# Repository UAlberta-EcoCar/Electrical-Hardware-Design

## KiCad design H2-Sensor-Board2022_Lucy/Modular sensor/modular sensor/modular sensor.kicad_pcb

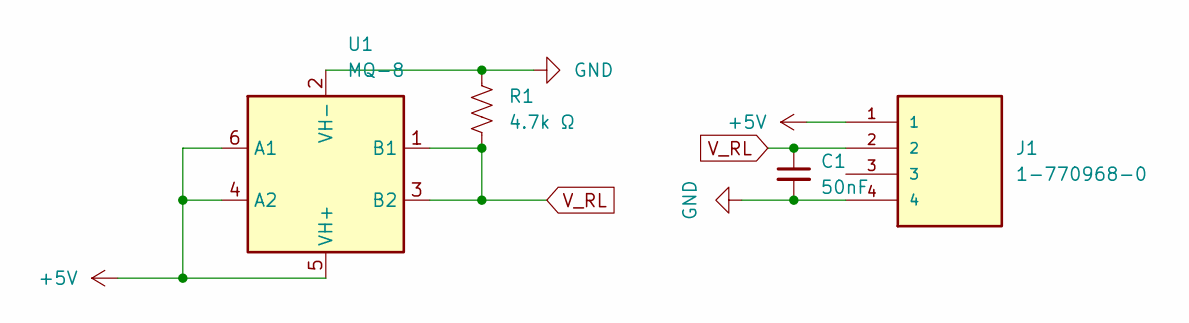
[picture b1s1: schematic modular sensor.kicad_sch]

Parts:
C1: 50nF; C_0402_1005Metric
J1: 1-770968-0; TE_1-770968-0
R1: 4.7k Ω; R_0402_1005Metric_Pad0.72x0.64mm_HandSolder
U1: MQ-8

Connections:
+5V: J1.1, U1.4 (A2), U1.5 (VH+), U1.6 (A1)
GND: C1.2, J1.4, R1.1, U1.2 (VH-)
V_RL: C1.1, J1.2, R1.2, U1.1 (B1), U1.3 (B2)

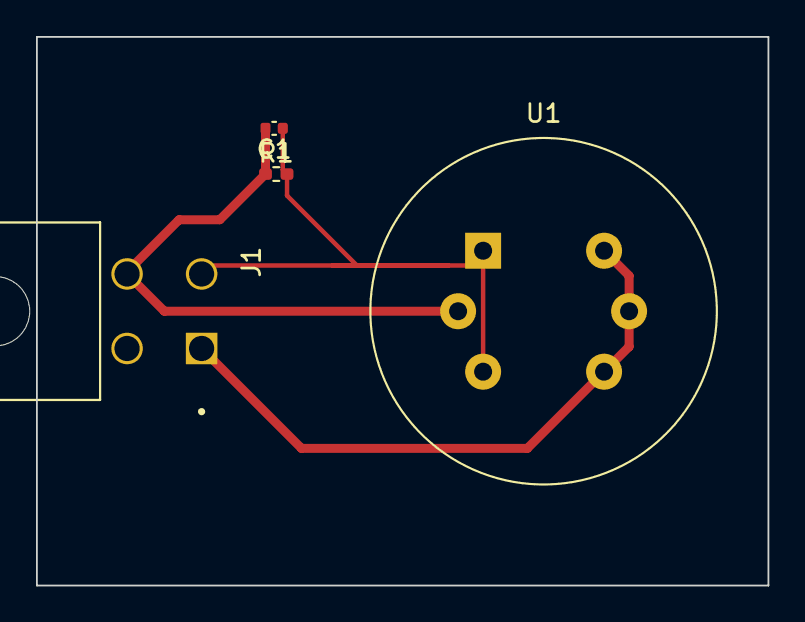
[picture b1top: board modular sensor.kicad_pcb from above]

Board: 2 copper layers, 40.6 x 30.5 mm, 4 parts (0 on the bottom side), 3 nets.

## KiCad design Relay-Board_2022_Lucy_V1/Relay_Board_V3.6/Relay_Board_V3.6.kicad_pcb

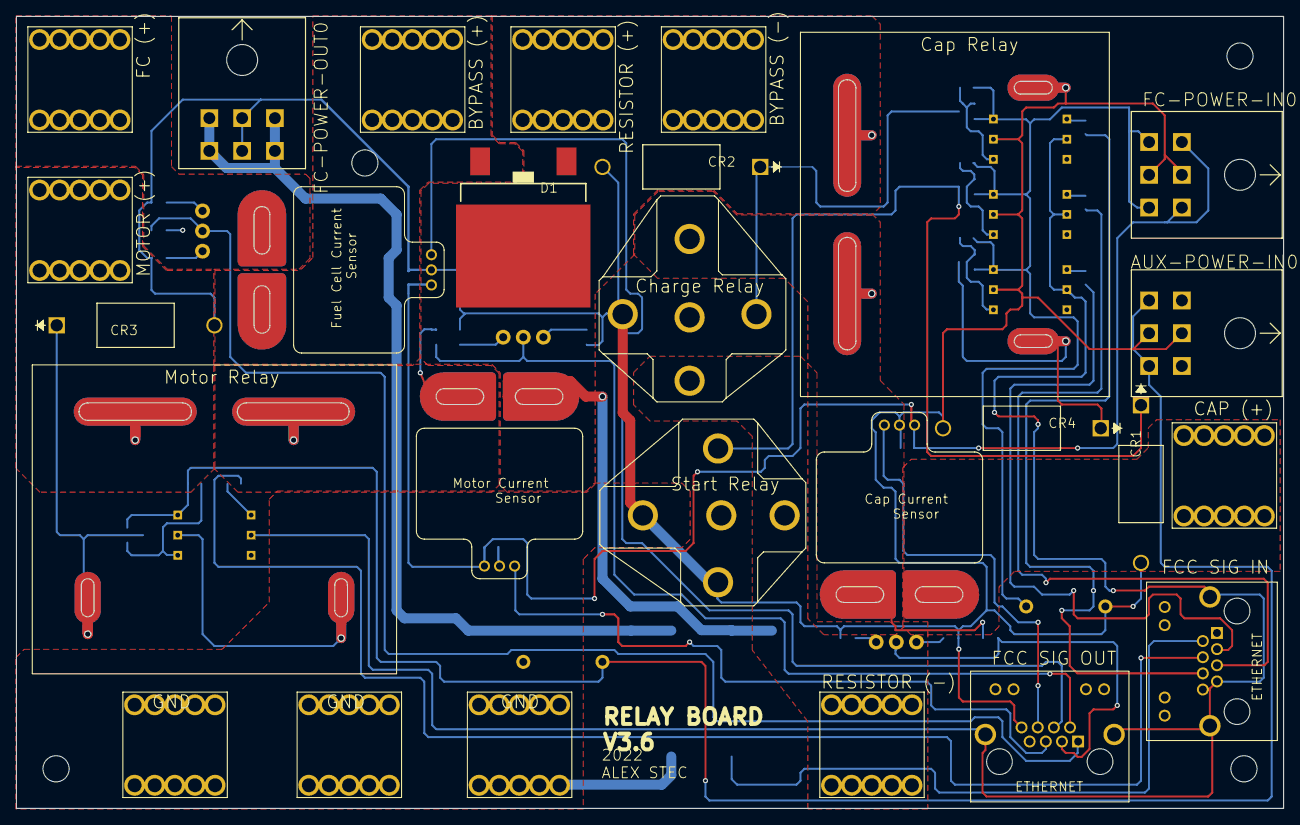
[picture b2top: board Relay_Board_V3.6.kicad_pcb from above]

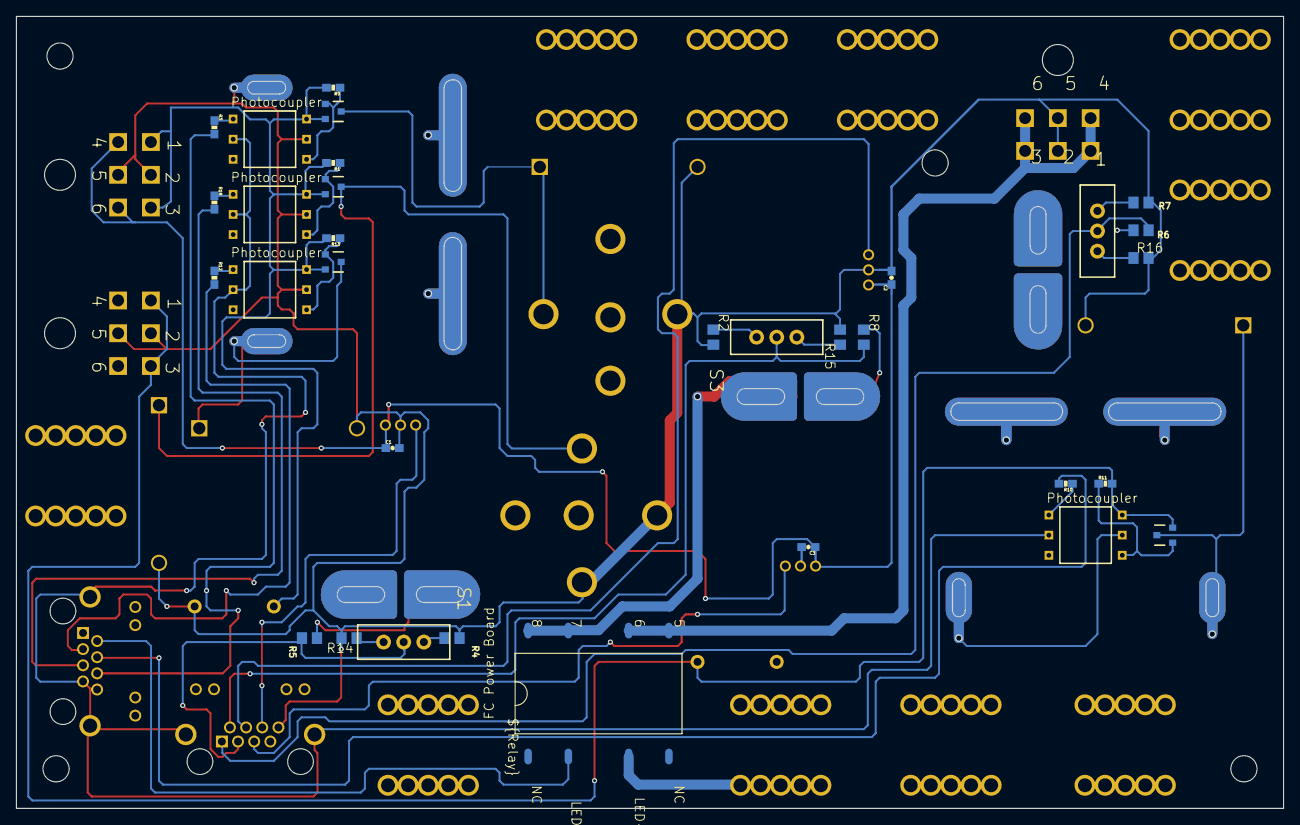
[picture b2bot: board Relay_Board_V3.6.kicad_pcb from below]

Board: 2 copper layers, 160.0 x 100.0 mm, 65 parts (32 on the bottom side), 44 nets.

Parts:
AUX-POWER-IN0: TE_6-PIN
C1, C2, C3: 0.1u; 0603-CAP
CAP.GND0, CAP.POS0, CAP.POS1, CAP.POS2: 732-3204-ND_CONNECTOR; 732-3204-ND
CR1, CR2, CR3, CR4: MUR420RLG; DO-201AD
D1: APT60S20SG; TO268
FC-POWER-IN0: TE_6-PIN
FC-POWER-OUT0: TE_6-PIN
FC.GND0, FC.POS0: 732-3204-ND_CONNECTOR; 732-3204-ND
FCC_SIG_IN0: ETHERNET; A122645-ND
FCC_SIG_OUT0: ETHERNET; A122645-ND
FC_POWER_BOARD_RELAY0: RELAY-CPC1907B
MOTOR.GROUND0, MOTOR.POSITIVE0: 732-3204-ND_CONNECTOR; 732-3204-ND
R1, R9, R11, R13: 10k; 0603-RES
R2, R4, R7: 775 (0.1%); R0805
R3, R10, R12, R18: 470; 0603-RES
R5, R6, R8: 10.5k (0.1%); R0805
R14, R15, R16: 1.5k (0.1%); R0805
RES.NEG0, RES.POS0: 732-3204-ND_CONNECTOR; 732-3204-ND
S1, S2, S3: SWITCH-SPDT
START.RELAY1, START.RELAY2: VCF4-1000
U$1, U$3, U$5, U$11: DMP3056L-7DMP3056L-7; DMP3056L-7
U$2, U$4, U$6, U$12: H11L1H11L1; H11L1
U$7, U$8, U$9: ACS770LCB_CURRENTSENSOR
U$13, U$14: 255-5246-ND
U$15, U$16: P6KE15A-E3/54GICT-ND_TVS_DIODE; P6KE15A-E3_54GICT-ND_TVS_DIODE
U$18, U$20, U$21, U$23: STAND-OFF

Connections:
5V: C1.1, C2.1, C3.1, FC-POWER-IN0.4, FC-POWER-IN0.6, U$7.PIN1, U$8.PIN1, U$9.PIN1
AUX.12: AUX-POWER-IN0.1, AUX-POWER-IN0.3, R11.2, U$3.S, U$4.VCC, U$16.P$2
CAP_CURR: FCC_SIG_OUT0.P$6, U$8.PIN3
CAP_FUSE: CAP.POS0.P$1, CAP.POS0.P$2, CAP.POS0.P$3, CAP.POS0.P$4, CAP.POS0.P$5, CAP.POS0.P$6, CAP.POS0.P$7, CAP.POS0.P$8, CAP.POS0.P$9, CAP.POS0.P$10, U$8.PIN5
CAP_R: FCC_SIG_IN0.P$3, R12.2
CAP_SENSOR: R5.1, START.RELAY2.30, U$8.PIN4, U$13.NO(+), U$13.NO(++)
CAP_VOLT: FCC_SIG_OUT0.P$3, R5.2, S1.2
CHARGE_R: FCC_SIG_IN0.P$6, R3.2
CHARGING_RES_NEG: RES.NEG0.P$1, RES.NEG0.P$2, RES.NEG0.P$3, RES.NEG0.P$4, RES.NEG0.P$5, RES.NEG0.P$6, RES.NEG0.P$7, RES.NEG0.P$8, RES.NEG0.P$9, RES.NEG0.P$10, START.RELAY1.87, START.RELAY2.87
FC.12: FC-POWER-IN0.1, FC-POWER-IN0.3, R1.2, R9.2, R13.2, U$1.S, U$2.VCC, U$5.S, U$6.VCC, U$11.S, U$12.VCC, U$15.P$2
FC_CURR: FCC_SIG_OUT0.P$4, U$7.PIN3
FC_POS: CAP.POS2.P$1, CAP.POS2.P$2, CAP.POS2.P$3, CAP.POS2.P$4, CAP.POS2.P$5, CAP.POS2.P$6, CAP.POS2.P$7, CAP.POS2.P$8, CAP.POS2.P$9, CAP.POS2.P$10, D1.(-), D1.C@1, D1.C@2, FC_POWER_BOARD_RELAY0.7, FC_POWER_BOARD_RELAY0.8, RES.POS0.P$1, RES.POS0.P$2, RES.POS0.P$3, RES.POS0.P$4, RES.POS0.P$5, RES.POS0.P$6, RES.POS0.P$7, RES.POS0.P$8, RES.POS0.P$9, RES.POS0.P$10, U$9.PIN4, U$13.NO(-), U$13.NO(--)
FC_POWER: CAP.POS1.P$1, CAP.POS1.P$2, CAP.POS1.P$3, CAP.POS1.P$4, CAP.POS1.P$5, CAP.POS1.P$6, CAP.POS1.P$7, CAP.POS1.P$8, CAP.POS1.P$9, CAP.POS1.P$10, D1.(+), U$7.PIN5
FC_POWER_OUT: FC-POWER-OUT0.1, FC-POWER-OUT0.3, FC-POWER-OUT0.4, FC-POWER-OUT0.6, FC_POWER_BOARD_RELAY0.5, FC_POWER_BOARD_RELAY0.6
FC_R: FCC_SIG_IN0.P$2, FC_POWER_BOARD_RELAY0.LED+
FC_SENSOR: FC.POS0.P$1, FC.POS0.P$2, FC.POS0.P$3, FC.POS0.P$4, FC.POS0.P$5, FC.POS0.P$6, FC.POS0.P$7, FC.POS0.P$8, FC.POS0.P$9, FC.POS0.P$10, R6.1, U$7.PIN4
FC_VOLT: FCC_SIG_OUT0.P$1, R6.2, S2.2
GND: AUX-POWER-IN0.2, AUX-POWER-IN0.5, C1.2, C2.2, C3.2, CAP.GND0.P$1, CAP.GND0.P$2, CAP.GND0.P$3, CAP.GND0.P$4, CAP.GND0.P$5, CAP.GND0.P$6, CAP.GND0.P$7, CAP.GND0.P$8, CAP.GND0.P$9, CAP.GND0.P$10, CR1.2, CR2.2, CR3.2, CR4.2, FC-POWER-IN0.2, FC-POWER-IN0.5, FC-POWER-OUT0.2, FC-POWER-OUT0.5, FC.GND0.P$1, FC.GND0.P$2, FC.GND0.P$3, FC.GND0.P$4, FC.GND0.P$5, FC.GND0.P$6, FC.GND0.P$7, FC.GND0.P$8, FC.GND0.P$9, FC.GND0.P$10, FCC_SIG_OUT0.P$8, FC_POWER_BOARD_RELAY0.LED-, MOTOR.GROUND0.P$1, MOTOR.GROUND0.P$2, MOTOR.GROUND0.P$3, MOTOR.GROUND0.P$4, MOTOR.GROUND0.P$5, MOTOR.GROUND0.P$6, MOTOR.GROUND0.P$7, MOTOR.GROUND0.P$8, MOTOR.GROUND0.P$9, MOTOR.GROUND0.P$10, R2.2, R4.2, R7.2, R14.2, R15.2, R16.2, START.RELAY1.30, START.RELAY1.85, START.RELAY2.85, U$2.GND, U$4.GND, U$6.GND, U$7.PIN2, U$8.PIN2, U$9.PIN2, U$12.GND, U$13.(-), U$13.(--), U$14.(-), U$14.(--), U$15.P$1, U$16.P$1
ISO_GND: FCC_SIG_IN0.P$7, FCC_SIG_IN0.P$8, FCC_SIG_IN0.P$13, FCC_SIG_IN0.P$14, FCC_SIG_OUT0.P$13, FCC_SIG_OUT0.P$14, U$2.CATHODE, U$4.CATHODE, U$6.CATHODE, U$12.CATHODE
MOTOR_CURR: FCC_SIG_OUT0.P$5, U$9.PIN3
MOTOR_C_SENSOR: R8.1, U$9.PIN5, U$14.NO(-), U$14.NO(--)
MOTOR_POS: MOTOR.POSITIVE0.P$1, MOTOR.POSITIVE0.P$2, MOTOR.POSITIVE0.P$3, MOTOR.POSITIVE0.P$4, MOTOR.POSITIVE0.P$5, MOTOR.POSITIVE0.P$6, MOTOR.POSITIVE0.P$7, MOTOR.POSITIVE0.P$8, MOTOR.POSITIVE0.P$9, MOTOR.POSITIVE0.P$10, U$14.NO(+), U$14.NO(++)
MOTOR_R: FCC_SIG_IN0.P$4, R10.2
MOTOR_VOLT: FCC_SIG_OUT0.P$2, R8.2, S3.2
unnamed: R9.1, U$1.G, U$2.VO
unnamed: R3.1, U$2.ANODE
unnamed: CR2.1, START.RELAY2.86, U$1.D
unnamed: R11.1, U$3.G, U$4.VO
unnamed: R10.1, U$4.ANODE
unnamed: CR3.1, U$3.D, U$14.(+), U$14.(++)
unnamed: R13.1, U$5.G, U$6.VO
unnamed: R12.1, U$6.ANODE
unnamed: R4.1, S1.1
unnamed: R14.1, S1.3
unnamed: R2.1, S3.1
unnamed: R15.1, S3.3
unnamed: CR4.1, U$5.D, U$13.(+), U$13.(++)
unnamed: R7.1, S2.1
unnamed: R16.1, S2.3
unnamed: R1.1, U$11.G, U$12.VO
unnamed: R18.1, U$12.ANODE
unnamed: CR1.1, START.RELAY1.86, U$11.D
NC: FCC_SIG_IN0.P$1, FCC_SIG_OUT0.P$7
START_R: FCC_SIG_IN0.P$5, R18.2

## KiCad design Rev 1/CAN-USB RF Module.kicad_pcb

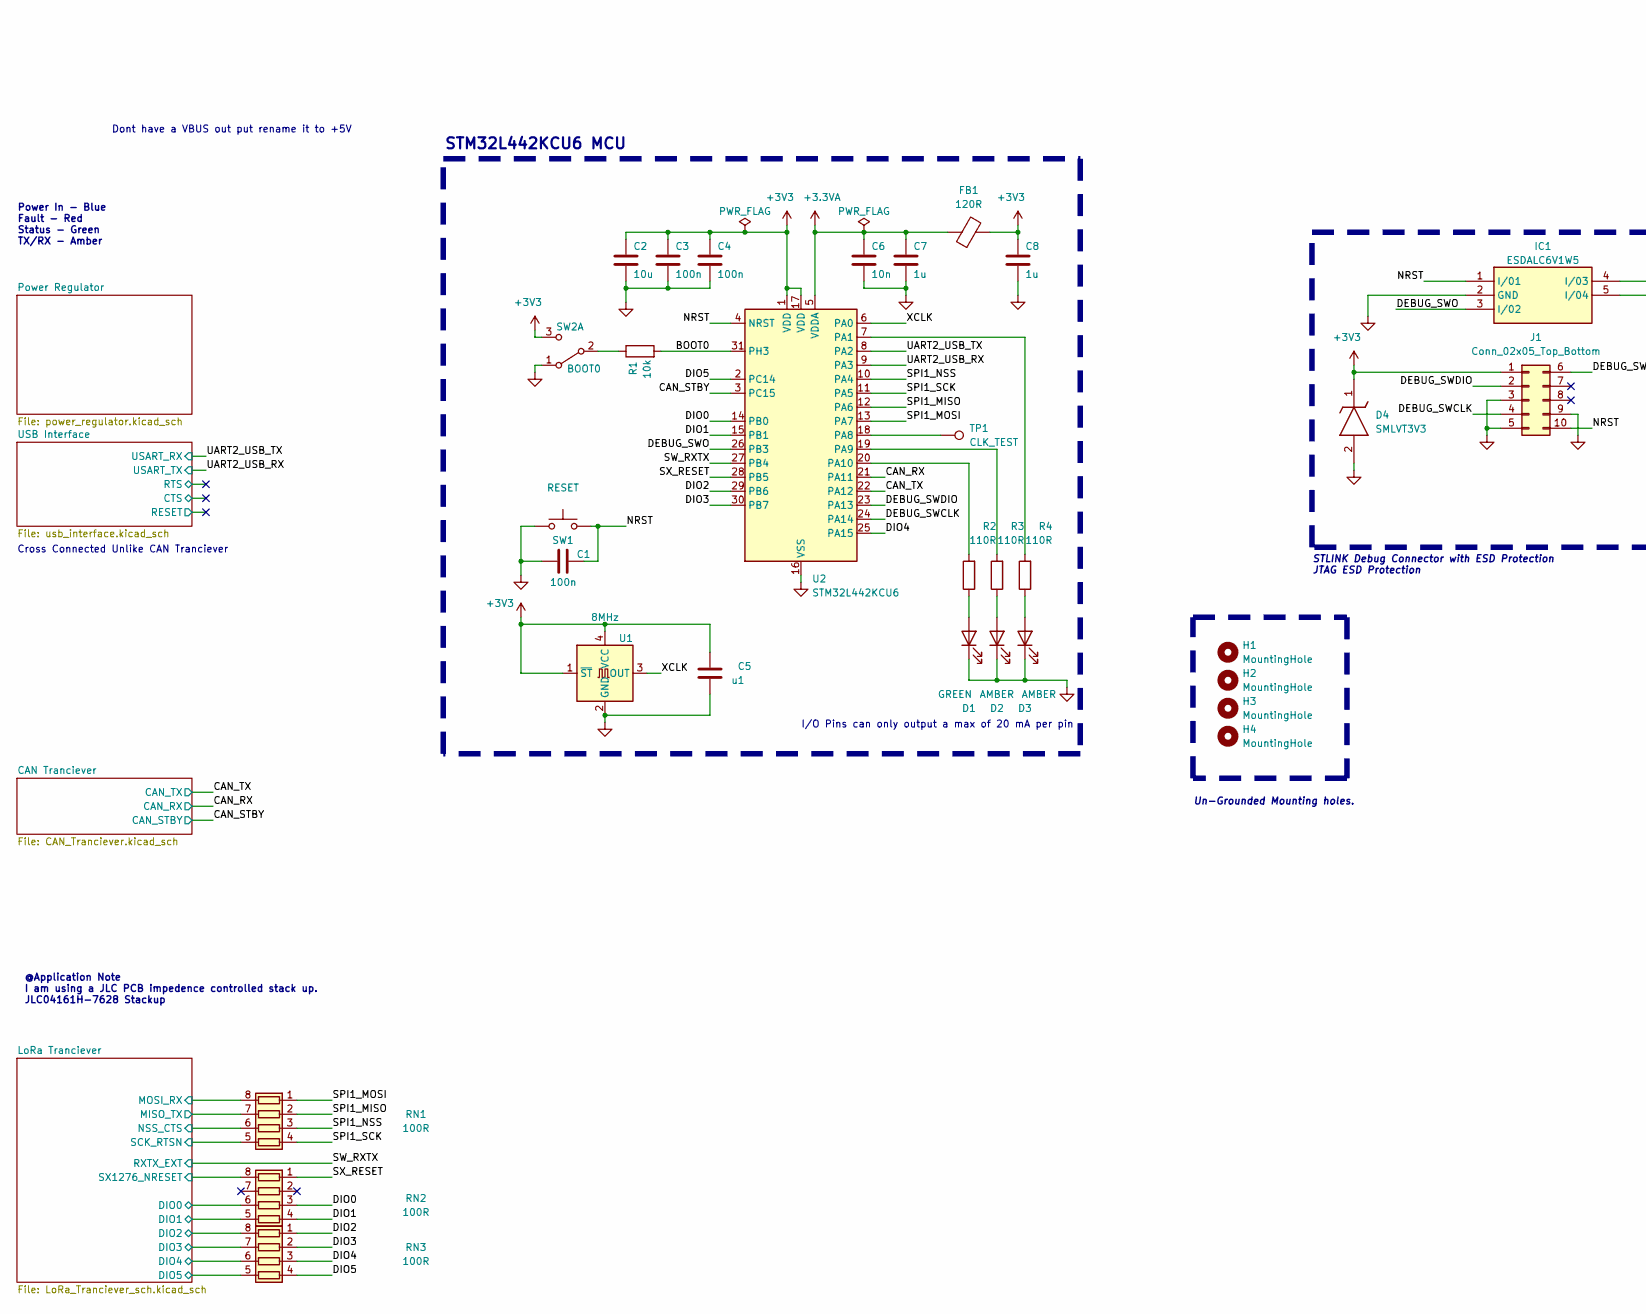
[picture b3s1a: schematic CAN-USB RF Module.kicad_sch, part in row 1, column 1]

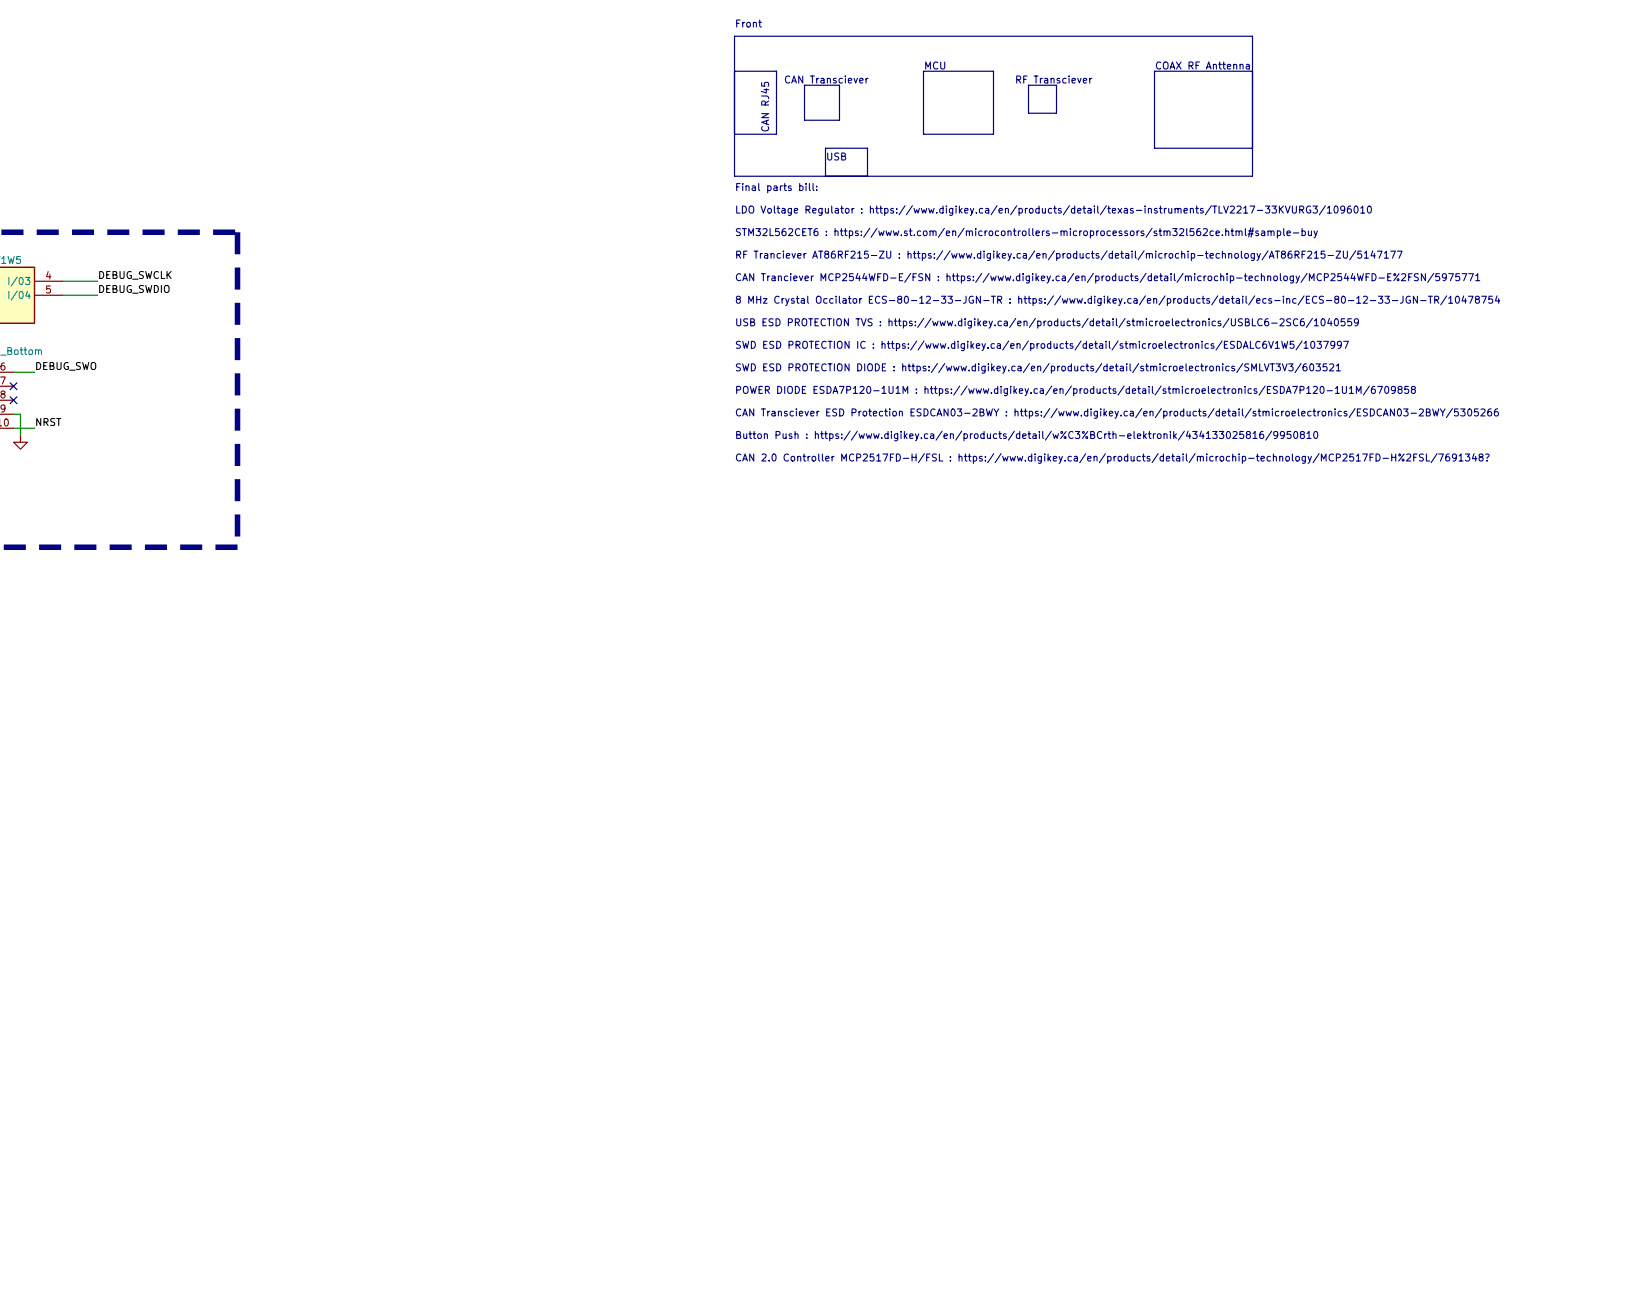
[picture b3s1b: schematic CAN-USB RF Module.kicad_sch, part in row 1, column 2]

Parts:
C1, C3, C4: 100n; C_0402_1005Metric; LCSC # C1525
C2: 10u; C_0805_2012Metric; MPN CL21B106KOQNNNE; LCSC # C95841
C5: u1; C_0402_1005Metric; LCSC # C541464
C6: 10n; C_0402_1005Metric; LCSC # C1525
C7, C8: 1u; C_0402_1005Metric; LCSC # C528974
D1: GREEN; LED_0603_1608Metric; LCSC # C72043
D2, D3: AMBER; LED_0603_1608Metric; LCSC # C2842814
D4: SMLVT3V3; DIOM5436X265N; LCSC # C283619
FB1: 120R; R_0603_1608Metric; LCSC # C62708
H1, H2, H3, H4: MountingHole; MountingHole_2.2mm_M2
IC1: ESDALC6V1W5; SOT65P210X110-5N; LCSC # C2827626
J1: Conn_02x05_Top_Bottom; PinHeader_2x05_P2.54mm_Vertical; LCSC # C5116482
R1: 10k; R_0603_1608Metric; LCSC # C25531
R2, R3, R4: 110R; R_0603_1608Metric; LCSC # C138064
RN1, RN2, RN3: 100R; R_Array_Concave_4x0402; LCSC # C48442
SW1: RESET; SW_SPST_PTS810; LCSC # C221896
SW2: BOOT0; SW_SPDT_PCM12; LCSC # C221841
TP1: CLK_TEST; TestPoint_Pad_D1.0mm
U1: 8MHz; Crystal_SMD_3225-4Pin_3.2x2.5mm; LCSC # C558766
U2: STM32L442KCU6; QFN-32-1EP_5x5mm_P0.5mm_EP3.45x3.45mm; LCSC # C2969865

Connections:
+3.3VA: C6.1, C7.1, FB1.1, U2.5 (VDDA)
+3V3: C2.1, C3.1, C4.1, C5.2, C8.1, D4.1 (K), FB1.2, J1.1, SW2.3 (C), U1.1 (~ST), U1.4 (VCC), U2.1 (VDD), U2.17 (VDD); also elsewhere on the board
/BOOT0: R1.2, U2.31 (PH3)
/CAN_RX: U2.21 (PA11); also elsewhere on the board
/CAN_STBY: U2.3 (PC15); also elsewhere on the board
/CAN_TX: U2.22 (PA12); also elsewhere on the board
/DEBUG_SWCLK: IC1.4 (I/03), J1.4, U2.24 (PA14)
/DEBUG_SWDIO: IC1.5 (I/04), J1.2, U2.23 (PA13)
/DEBUG_SWO: IC1.3 (I/02), J1.6, U2.26 (PB3)
/DIO0: RN2.3 (R3.1), U2.14 (PB0)
/DIO1: RN2.4 (R4.1), U2.15 (PB1)
/DIO2: RN3.1 (R1.1), U2.29 (PB6)
/DIO3: RN3.2 (R2.1), U2.30 (PB7)
/DIO4: RN3.3 (R3.1), U2.25 (PA15)
/DIO5: RN3.4 (R4.1), U2.2 (PC14)
/LoRa Tranciever/DIO0: RN2.6 (R3.2); also elsewhere on the board
/LoRa Tranciever/DIO1: RN2.5 (R4.2); also elsewhere on the board
/LoRa Tranciever/DIO2: RN3.8 (R1.2); also elsewhere on the board
/LoRa Tranciever/DIO3: RN3.7 (R2.2); also elsewhere on the board
/LoRa Tranciever/DIO4: RN3.6 (R3.2); also elsewhere on the board
/LoRa Tranciever/DIO5: RN3.5 (R4.2); also elsewhere on the board
/LoRa Tranciever/MISO_TX: RN1.7 (R2.2); also elsewhere on the board
/LoRa Tranciever/MOSI_RX: RN1.8 (R1.2); also elsewhere on the board
/LoRa Tranciever/NSS_CTS: RN1.6 (R3.2); also elsewhere on the board
/LoRa Tranciever/SCK_RTSN: RN1.5 (R4.2); also elsewhere on the board
/LoRa Tranciever/SX1276_NRESET: RN2.8 (R1.2); also elsewhere on the board
/NRST: C1.2, IC1.1 (I/01), J1.10, SW1.2, U2.4 (NRST)
/SPI1_MISO: RN1.2 (R2.1), U2.12 (PA6)
/SPI1_MOSI: RN1.1 (R1.1), U2.13 (PA7)
/SPI1_NSS: RN1.3 (R3.1), U2.10 (PA4)
/SPI1_SCK: RN1.4 (R4.1), U2.11 (PA5)
/SW_RXTX: U2.27 (PB4); also elsewhere on the board
/SX_RESET: RN2.1 (R1.1), U2.28 (PB5)
/UART2_USB_RX: U2.9 (PA3); also elsewhere on the board
/UART2_USB_TX: U2.8 (PA2); also elsewhere on the board
/XCLK: U1.3 (OUT), U2.6 (PA0)
GND: C1.1, C2.2, C3.2, C4.2, C5.1, C6.2, C7.2, C8.2, D1.1 (K), D2.1 (K), D3.1 (K), D4.2 (A), IC1.2 (GND), J1.3, J1.5, J1.9, SW1.1, SW2.1 (A), U1.2 (GND), U2.16 (VSS), U2.32 (VSS), U2.33 (VSS); also elsewhere on the board
unnamed: D1.2 (A), R2.1
unnamed: D2.2 (A), R3.1
unnamed: D3.2 (A), R4.1
unnamed: R1.1, SW2.2 (B)
unnamed: R4.2, U2.7 (PA1)
unnamed: TP1.1, U2.18 (PA8)
unnamed: R3.2, U2.19 (PA9)
unnamed: R2.2, U2.20 (PA10)

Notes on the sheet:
MCU
Front
Un-Grounded Mounting holes.
COAX RF Anttenna
Final parts bill: LDO Voltage Regulator : https://www.digikey.ca/en/products/detail/texas-instruments/TLV2217-33KVURG3/1096010 STM32L562CET6 : https://www.st.com/en/microcontrollers-microprocessors/stm32l562ce.html#sample-buy RF Tranciever AT86RF215-ZU : https://www.digikey.ca/en/products/detail/mi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
STM32L442KCU6 MCU
CAN Transciever
STLINK Debug Connector with ESD Protection JTAG ESD Protection
@Application Note I am using a JLC PCB impedence controlled stack up. JLC04161H-7628 Stackup
Power In - Blue Fault - Red Status - Green TX/RX - Amber
USB
Cross Connected Unlike CAN Tranciever
I/O Pins can only output a max of 20 mA per pin
CAN RJ45
RF Transciever
Dont have a VBUS out put rename it to +5V

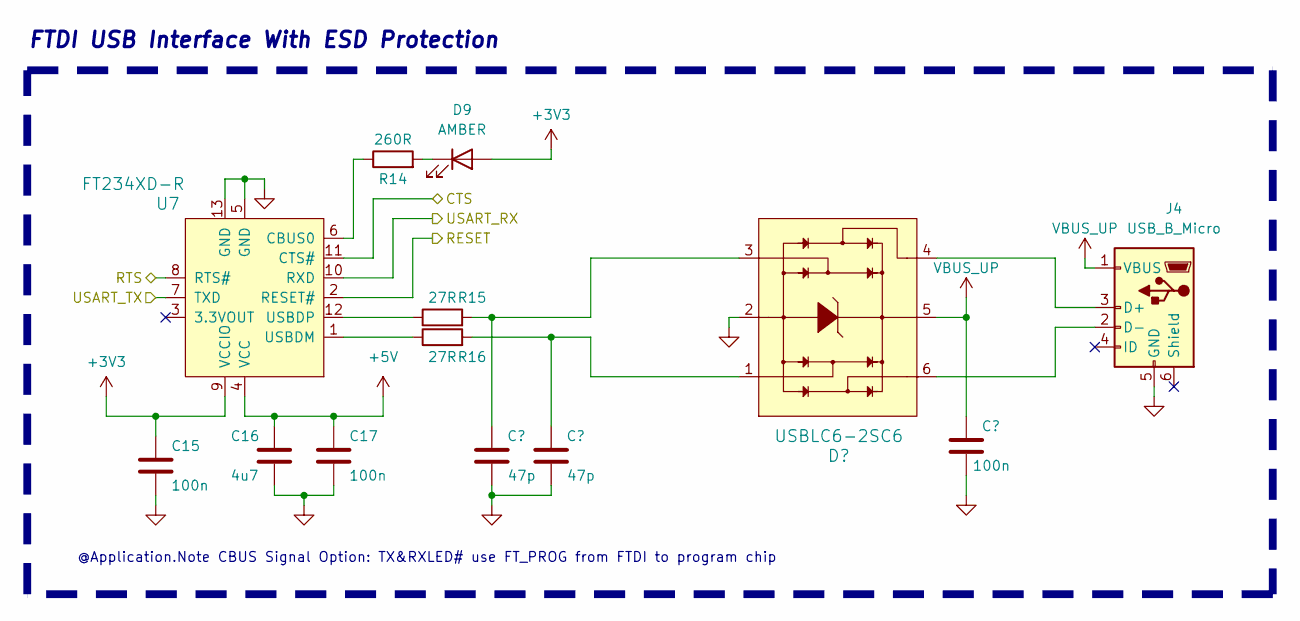
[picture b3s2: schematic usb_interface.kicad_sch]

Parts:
C15, C17, C20: 100n; C_0402_1005Metric; LCSC # C1525
C16: 4u7; C_0603_1608Metric; LCSC # C307423
C18, C19: 47p; C_0402_1005Metric; LCSC # C1567
D9: AMBER; LED_0603_1608Metric; LCSC # C2842814
D10: USBLC6-2SC6; SOT23-6L; LCSC # C7519
J4: USB_B_Micro; USB_Micro-B_Amphenol_10118194_Horizontal; LCSC # C428495
R14: 260R; R_0603_1608Metric; LCSC # C22966
R15, R16: 27R; R_0603_1608Metric; LCSC # C25190
U7: FT234XD-R; DFN-12-1EP_3x3mm; LCSC # C132158

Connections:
+3V3: C15.1, D9.2 (A), U7.9 (VCCIO); also elsewhere on the board
+5V: C16.1, C17.1, U7.4 (VCC); also elsewhere on the board
/UART2_USB_RX: U7.7 (TXD); also elsewhere on the board
/UART2_USB_TX: U7.10 (RXD); also elsewhere on the board
/USB Interface/CTS: U7.11 (CTS#)
/USB Interface/RESET: U7.2 (RESET#)
/USB Interface/RTS: U7.8 (RTS#)
GND: C15.2, C16.2, C17.2, C18.1, C19.1, C20.1, D10.2, J4.5 (GND), U7.5 (GND), U7.13 (GND); also elsewhere on the board
unnamed: C18.2, D10.3, R15.2
unnamed: C19.2, D10.1, R16.2
unnamed: D9.1 (K), R14.2
unnamed: D10.4, J4.3 (D+)
unnamed: D10.6, J4.2 (D-)
unnamed: R14.1, U7.6 (CBUS0)
unnamed: R16.1, U7.1 (USBDM)
unnamed: R15.1, U7.12 (USBDP)
VBUS_UP: C20.2, D10.5, J4.1 (VBUS); also elsewhere on the board

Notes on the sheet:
FTDI USB Interface With ESD Protection
@Application.Note CBUS Signal Option: TX&RXLED# use FT_PROG from FTDI to program chip

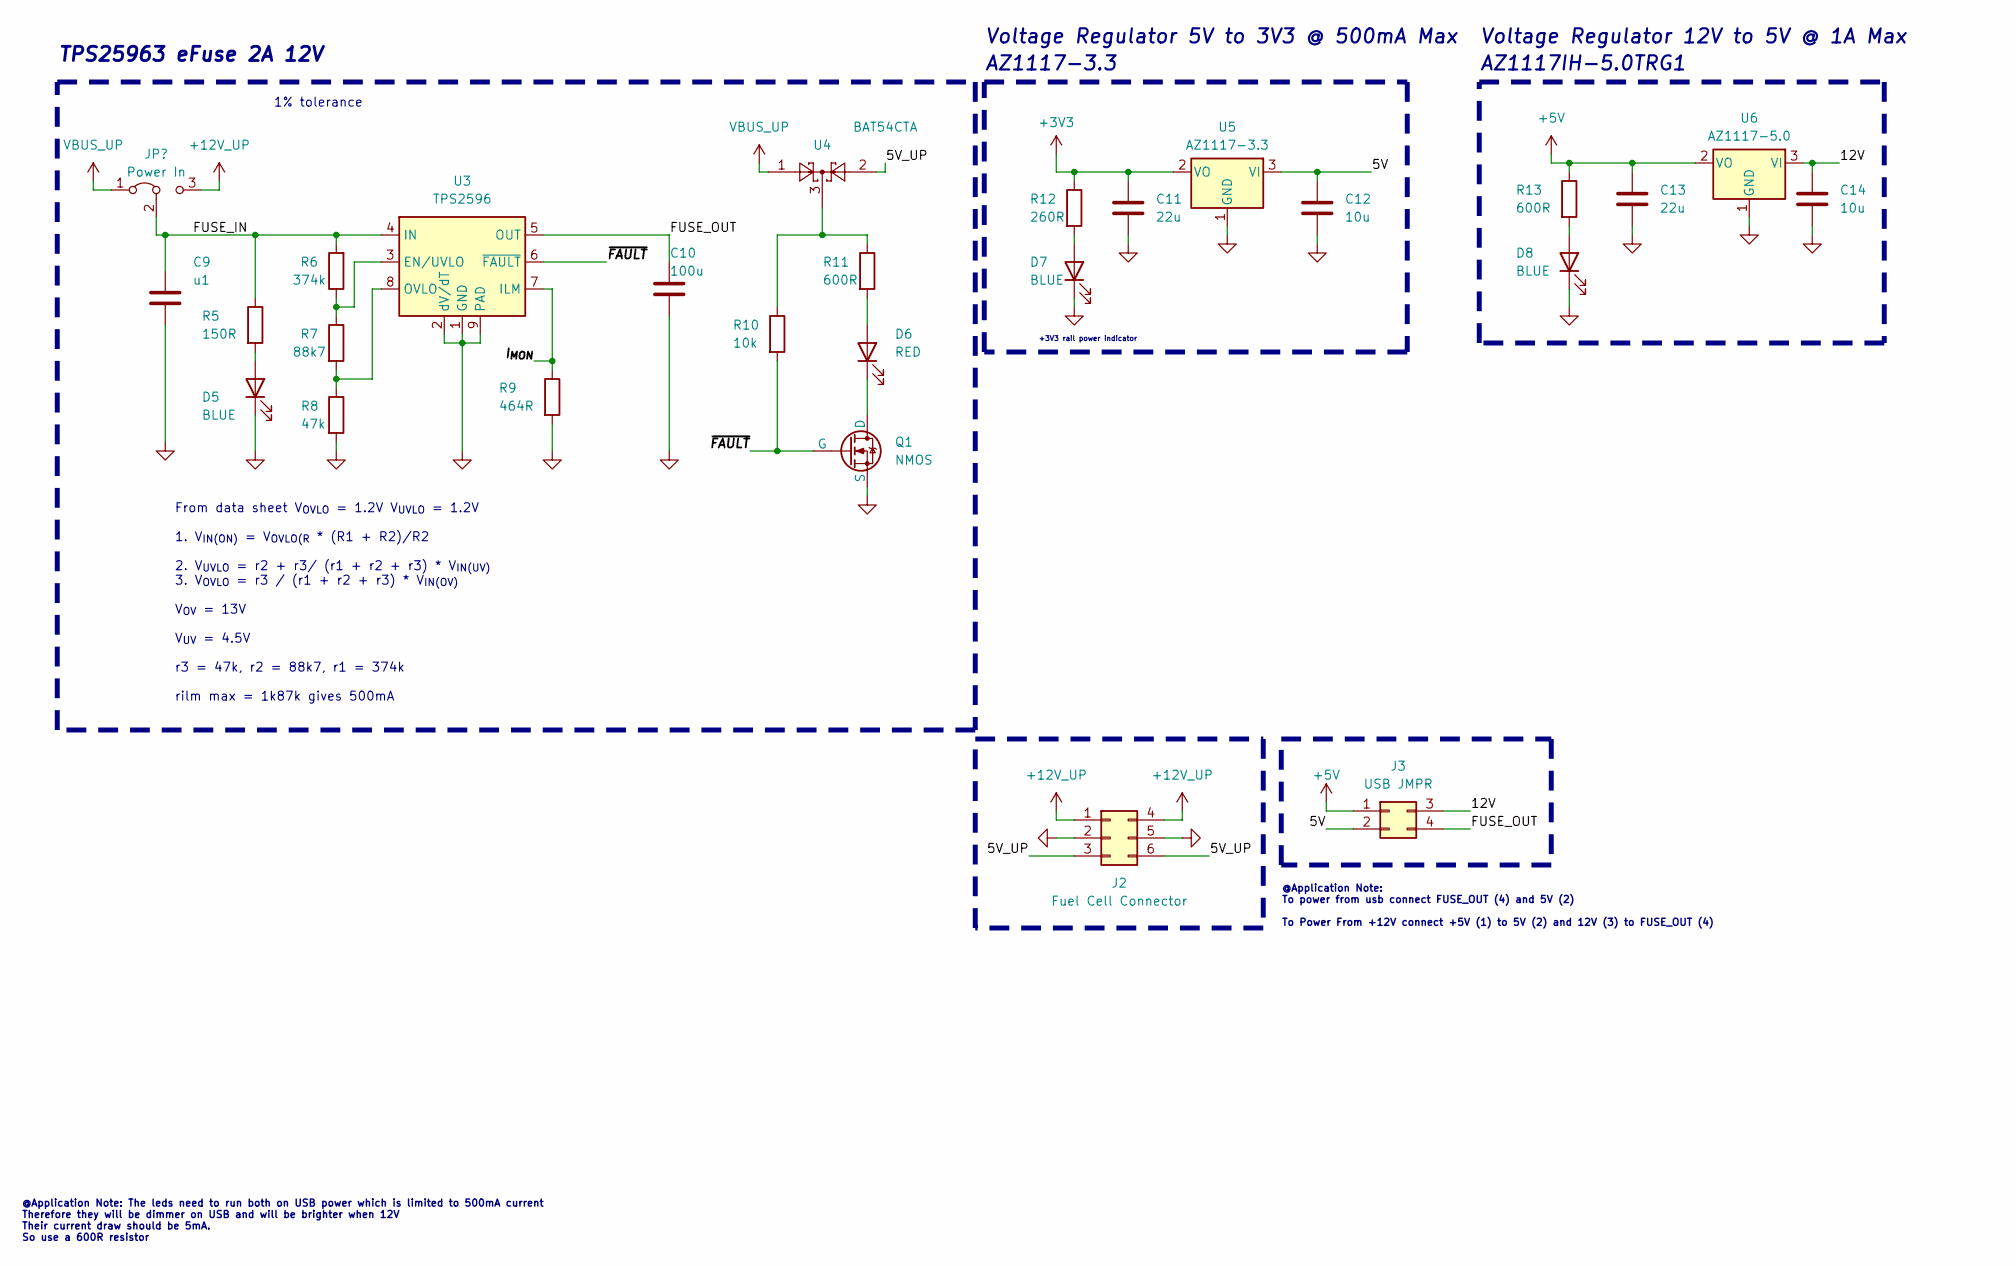
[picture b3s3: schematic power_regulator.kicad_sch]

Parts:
C9: u1; C_0603_1608Metric; JLCPCB Part#(optional) C30926
C10: 100u; CP_Elec_6.3x5.9; JLCPCB Part#(optional) C30926
C11, C13: 22u; C_0603_1608Metric; LCSC # C415703
C12, C14: 10u; C_0805_2012Metric; LCSC # C95841
D5: BLUE; LED_0603_1608Metric; JLCPCB Part#(optional) C965807
D6: RED; LED_0603_1608Metric; LCSC # C434419
D7, D8: BLUE; LED_0603_1608Metric; LCSC # C965807
J2: Fuel Cell Connector; Molex_Micro-Fit_3.0_43045-0621_2x03-1MP_P3.00mm_Horizontal; LCSC # C476812
J3: USB JMPR; PinHeader_2x02_P2.54mm_Vertical; LCSC # C5116482
JP1: Power In; PinHeader_1x03_P2.54mm_Vertical; LCSC # C5116482
Q1: NMOS; SOT-523; LCSC # C475757
R5: 150R; R_0603_1608Metric; JLCPCB Part#(optional) C114608
R6: 374k; R_0603_1608Metric; JLCPCB Part#(optional) C5713287
R7: 88k7; R_0603_1608Metric; JLCPCB Part#(optional) C228086
R8: 47k; R_0603_1608Metric; JLCPCB Part#(optional) C111134
R9: 464R; R_0603_1608Metric; JLCPCB Part#(optional) C5159701
R10: 10k; R_0603_1608Metric; LCSC # C25804
R11, R13: 600R; R_0603_1608Metric; LCSC # C2907058
R12: 260R; R_0603_1608Metric; LCSC # C22966
U3: TPS2596; TI_SO-PowerPAD-8; LCSC # C2155774
U4: BAT54CTA; SOT-23; LCSC # C460164
U5: AZ1117-3.3; SOT-223-3_TabPin2; LCSC # C110474
U6: AZ1117-5.0; SOT-223-3_TabPin2; LCSC # C99343

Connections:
+3V3: C11.1, R12.1, U5.2 (VO); also elsewhere on the board
+5V: C13.1, J3.1, R13.1, U6.2 (VO); also elsewhere on the board
+12V: J2.1, J2.4, JP1.3 (B)
/Power Regulator/5V: C12.1, J3.2, U5.3 (VI)
/Power Regulator/5V_UP: J2.3, J2.6, U4.2
/Power Regulator/12V: C14.1, J3.3, U6.3 (VI)
/Power Regulator/FUSE_IN: C9.1, JP1.2 (C), R5.1, R6.2, U3.4 (IN)
/Power Regulator/FUSE_OUT: C10.1, J3.4, U3.5 (OUT)
/Power Regulator/I_{MON}: R9.1, U3.7 (ILM)
/Power Regulator/~FAULT: Q1.2 (G), R10.2, U3.6 (~FAULT)
GND: C9.2, C10.2, C11.2, C12.2, C13.2, C14.2, D5.1 (K), D7.1 (K), D8.1 (K), J2.2, J2.5, Q1.3 (S), R8.2, R9.2, U3.1 (GND), U3.2 (dV/dT), U3.9 (PAD), U5.1 (GND), U6.1 (GND); also elsewhere on the board
unnamed: D5.2 (A), R5.2
unnamed: D6.2 (A), R11.2
unnamed: D6.1 (K), Q1.1 (D)
unnamed: D7.2 (A), R12.2
unnamed: D8.2 (A), R13.2
unnamed: R10.1, R11.1, U4.3
unnamed: R6.1, R7.1, U3.3 (EN/UVLO)
unnamed: R7.2, R8.1, U3.8 (OVLO)
VBUS_UP: JP1.1 (A), U4.1; also elsewhere on the board

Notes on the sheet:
TPS25963 eFuse 2A 12V
Voltage Regulator 5V to 3V3 @ 500mA Max
AZ1117-3.3
@Application Note: To power from usb connect FUSE_OUT (4) and 5V (2) To Power From +12V connect +5V (1) to 5V (2) and 12V (3) to FUSE_OUT (4)
From data sheet V_{OVLO} = 1.2V V_{UVLO} = 1.2V 1. V_{IN(ON)} = V_{OVLO(R} * (R1 + R2)/R2 2. V_{UVLO} = r2 + r3/ (r1 + r2 + r3) * V_{IN(UV)} 3. V_{OVLO} = r3 / (r1 + r2 + r3) * V_{IN(OV)} V_{OV} = 13V V_{UV} = 4.5V r3 = 47k, r2 = 88k7, r1 = 374k rilm max = 1k87k gives 500mA
AZ1117IH-5.0TRG1
1% tolerance
Voltage Regulator 12V to 5V @ 1A Max
@Application Note: The leds need to run both on USB power which is limited to 500mA current Therefore they will be dimmer on USB and will be brighter when 12V Their current draw should be 5mA. So use a 600R resistor
+3V3 rail power indicator

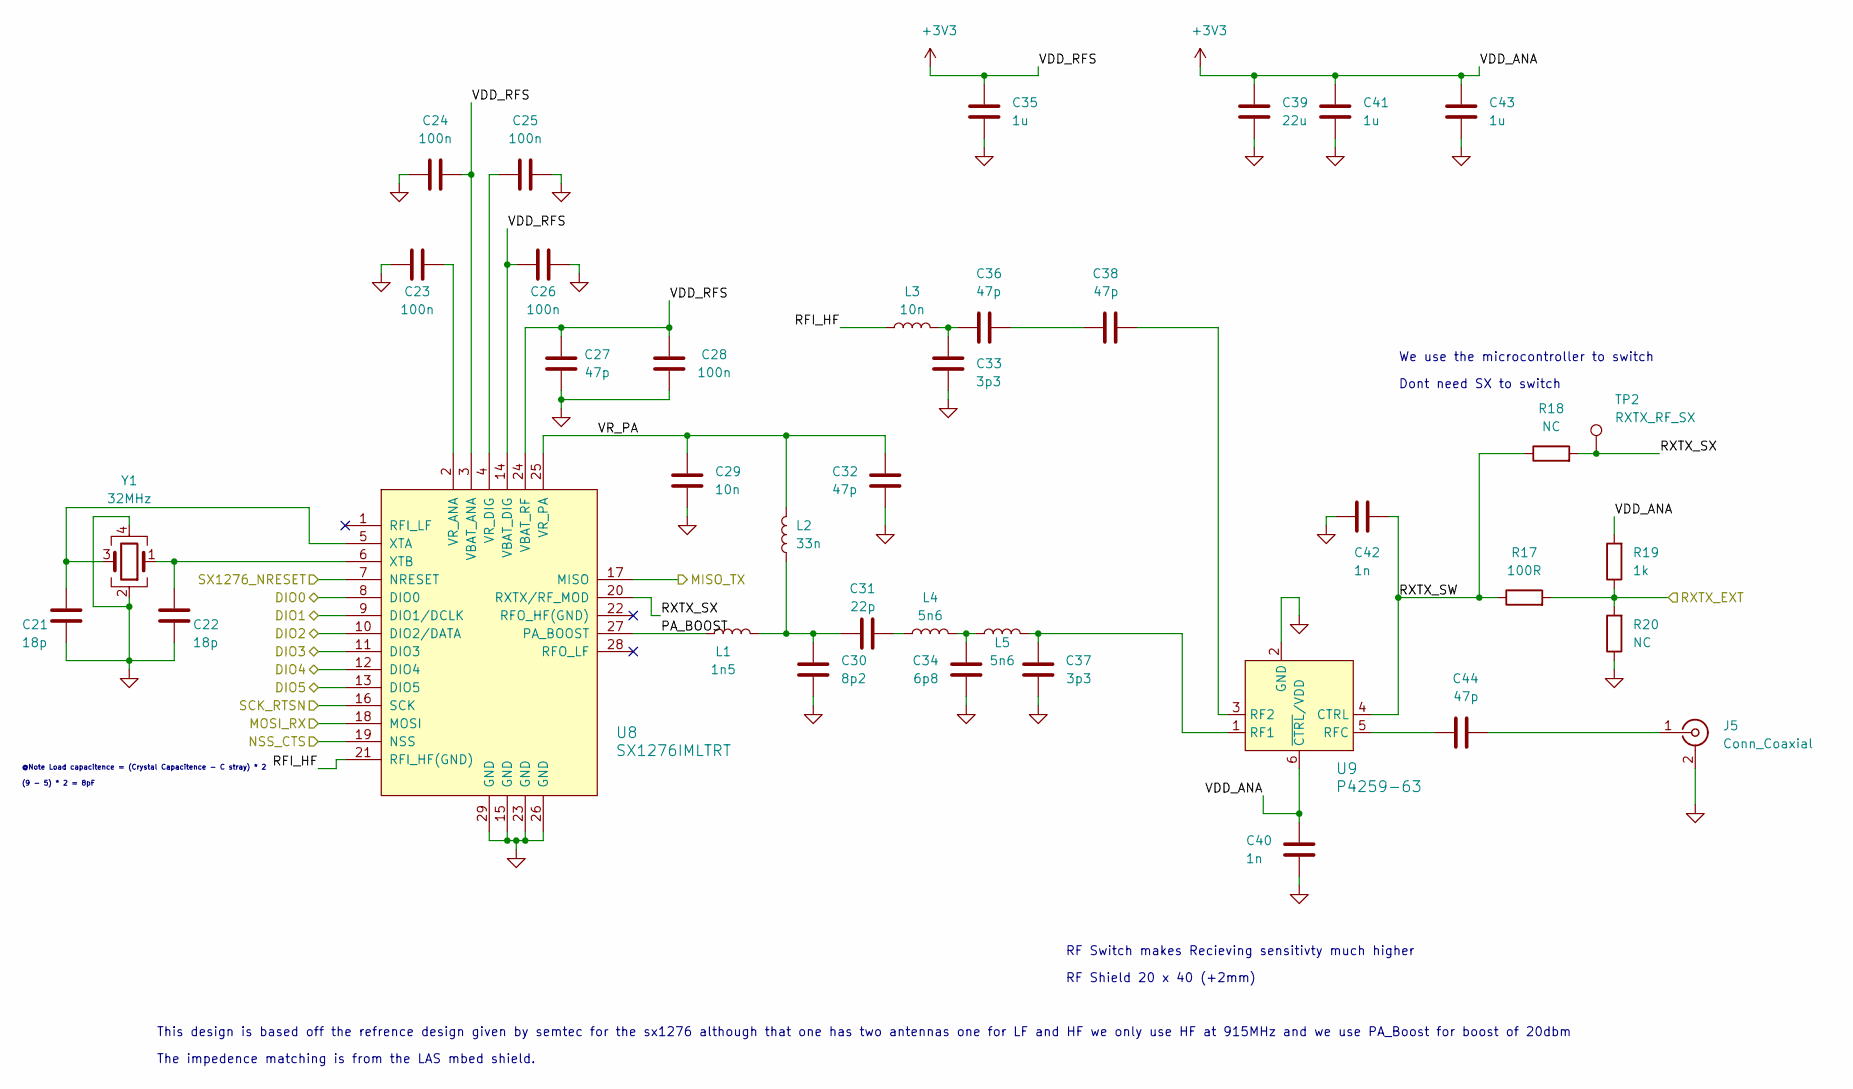
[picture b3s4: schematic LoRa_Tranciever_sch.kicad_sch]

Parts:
C21, C22: 18p; C_0402_1005Metric; LCSC # C1549
C23, C24, C25, C26, C28: 100n; C_0402_1005Metric; LCSC # C1525
C27, C32, C36, C38, C44: 47p; C_0402_1005Metric; LCSC # C1567
C29: 10n; C_0402_1005Metric; LCSC # C3855387
C30: 8p2; C_0402_1005Metric; LCSC # C1579
C31: 22p; C_0402_1005Metric; LCSC # C1555
C33, C37: 3p3; C_0402_1005Metric; LCSC # C710652
C34: 6p8; C_0402_1005Metric; LCSC # C1576
C35, C41, C43: 1u; C_0402_1005Metric; LCSC # C528974
C39: 22u; C_0603_1608Metric; LCSC # C415703
C40, C42: 1n; C_0402_1005Metric; LCSC # C106205
J5: Conn_Coaxial; TAOGLAS_EMPCB.SMAFSTJ.B.HT; LCSC # C1509221
L1: 1n5; L_0402_1005Metric; LCSC # C340346
L2: 33n; L_0402_1005Metric; LCSC # C86062
L3: 10n; L_0402_1005Metric; LCSC # C77103
L4, L5: 5n6; L_0402_1005Metric; LCSC # C91626
R17: 100R; R_0402_1005Metric; LCSC # C106233
R18, R20: NC; R_0402_1005Metric
R19: 1k; R_0402_1005Metric; LCSC # C21190
TP2: RXTX_RF_SX; TestPoint_Pad_D1.0mm
U8: SX1276IMLTRT; VQFN-28-1EP_6x6mm; LCSC # C80171
U9: P4259-63; SOT-363; LCSC # C470892
Y1: 32MHz; Crystal_SMD_2016-4Pin_2.0x1.6mm; LCSC # C1986260

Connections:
+3V3: C24.1, C26.1, C27.1, C28.1, C35.1, C39.1, C40.1, C41.1, C43.1, R19.2, U8.3 (VBAT_ANA), U8.14 (VBAT_DIG), U8.24 (VBAT_RF), U9.6 (~CTRL/VDD); also elsewhere on the board
/LoRa Tranciever/DIO0: U8.8 (DIO0); also elsewhere on the board
/LoRa Tranciever/DIO1: U8.9 (DIO1/DCLK); also elsewhere on the board
/LoRa Tranciever/DIO2: U8.10 (DIO2/DATA); also elsewhere on the board
/LoRa Tranciever/DIO3: U8.11 (DIO3); also elsewhere on the board
/LoRa Tranciever/DIO4: U8.12 (DIO4); also elsewhere on the board
/LoRa Tranciever/DIO5: U8.13 (DIO5); also elsewhere on the board
/LoRa Tranciever/MISO_TX: U8.17 (MISO); also elsewhere on the board
/LoRa Tranciever/MOSI_RX: U8.18 (MOSI); also elsewhere on the board
/LoRa Tranciever/NSS_CTS: U8.19 (NSS); also elsewhere on the board
/LoRa Tranciever/PA_BOOST: L1.1, U8.27 (PA_BOOST)
/LoRa Tranciever/RFI_HF: L3.1, U8.21 (RFI_HF(GND))
/LoRa Tranciever/RXTX_SW: C42.1, R17.1, R18.1, U9.4 (CTRL)
/LoRa Tranciever/RXTX_SX: R18.2, TP2.1, U8.20 (RXTX/RF_MOD)
/LoRa Tranciever/SCK_RTSN: U8.16 (SCK); also elsewhere on the board
/LoRa Tranciever/SX1276_NRESET: U8.7 (NRESET); also elsewhere on the board
/LoRa Tranciever/VR_PA: C29.1, C32.1, L2.2, U8.25 (VR_PA)
/SW_RXTX: R17.2, R19.1, R20.2; also elsewhere on the board
GND: C21.2, C22.2, C23.2, C24.2, C25.2, C26.2, C27.2, C28.2, C29.2, C30.2, C32.2, C33.2, C34.1, C35.2, C37.1, C39.2, C40.2, C41.2, C42.2, C43.2, J5.2 (Ext), R20.1, U8.15 (GND), U8.23 (GND), U8.26 (GND), U8.29 (GND), U9.2 (GND), Y1.2, Y1.4; also elsewhere on the board
unnamed: C30.1, C31.1, L1.2, L2.1
unnamed: C31.2, L4.1
unnamed: C33.1, C36.2, L3.2
unnamed: C34.2, L4.2, L5.1
unnamed: C36.1, C38.1
unnamed: C44.2, J5.1 (In)
unnamed: C23.1, U8.2 (VR_ANA)
unnamed: C25.1, U8.4 (VR_DIG)
unnamed: C21.1, U8.5 (XTA), Y1.3
unnamed: C22.1, U8.6 (XTB), Y1.1
unnamed: C37.2, L5.2, U9.1 (RF1)
unnamed: C38.2, U9.3 (RF2)
unnamed: C44.1, U9.5 (RFC)

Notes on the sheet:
The impedence matching is from the LAS mbed shield.
@Note Load capacitence = (Crystal Capacitence - C stray) * 2 (9 - 5) * 2 = 8pF
We use the microcontroller to switch
RF Shield 20 x 40 (+2mm)
This design is based off the refrence design given by semtec for the sx1276 although that one has two antennas one for LF and HF we only use HF at 915MHz and we use PA_Boost for boost of 20dbm
Dont need SX to switch
RF Switch makes Recieving sensitivty much higher
